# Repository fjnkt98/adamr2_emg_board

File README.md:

# adamr2_emg_board
PCB design project for the Emergency Stop Switch Mechanism of ADAMR2

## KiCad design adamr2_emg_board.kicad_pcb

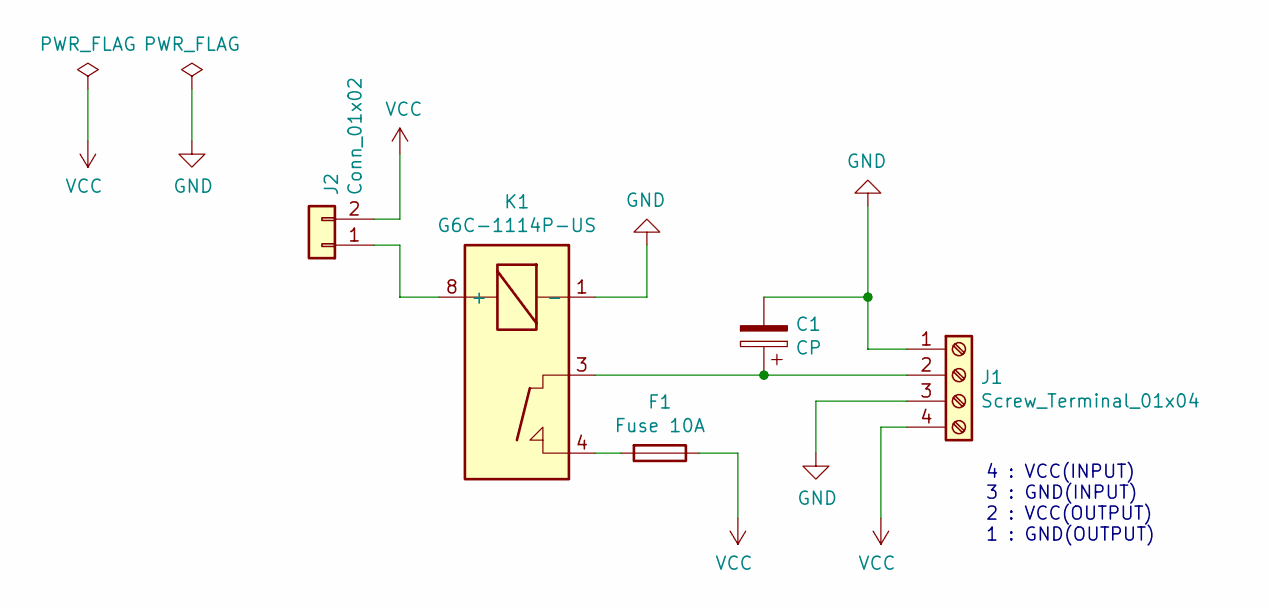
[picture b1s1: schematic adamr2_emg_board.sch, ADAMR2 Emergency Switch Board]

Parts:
C1: CP; UFG1H102MHM
F1: Fuse 10A; F-60-A
J1: Screw_Terminal_01x04; OSTYK21104030
J2: Conn_01x02; JST_XH_B2B-XH-A_1x02_P2.50mm_Vertical
K1: G6C-1114P-US

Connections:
GND: C1.2, J1.1, J1.3, K1.1 (-)
unnamed: C1.1, J1.2, K1.3
unnamed: F1.2, K1.4
unnamed: J2.1, K1.8 (+)
VCC: F1.1, J1.4, J2.2

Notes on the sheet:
4 : VCC(INPUT) 3 : GND(INPUT) 2 : VCC(OUTPUT) 1 : GND(OUTPUT)

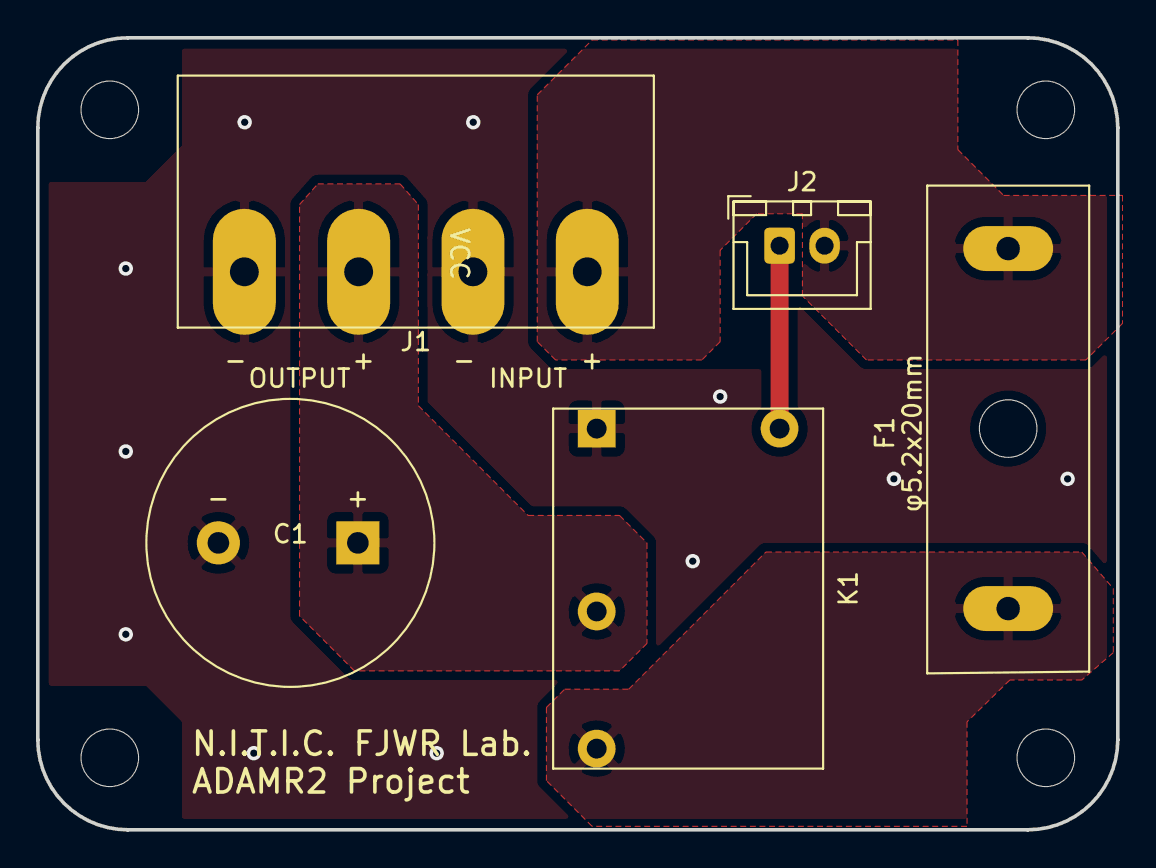
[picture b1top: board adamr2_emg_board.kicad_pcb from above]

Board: 2 copper layers, 60.0 x 44.0 mm, 5 parts (0 on the bottom side), 5 nets.

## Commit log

2020-08-03 Add: Initialize
2020-08-03 Update: フットプリントに3Dモデルを紐つけた
2020-08-03 Add: 4極ターミナルのフットプリント
2020-08-03 Add: 4極ターミナルの3Dモデルを追加
2020-08-03 Update: 3Dモデルを紐つけた
2020-08-03 Add: ミスミで買えるヒューズホルダ
2020-08-03 Add: ヒューズホルダの3Dモデル
2020-08-03 Update: ヒューズホルダの種類を変更した
2020-08-05 Update: フットプリントのパッドの形状を楕円に変更
2020-08-05 Update: 表面をVCC，裏面をGNDのベタにした
2020-08-07 Update: DRCに引っかかったので修正
    禁止領域の設定が配線と被っていたので形状を調整した
2020-08-10 Update: シルクを少し調整，寸法線を追加
2020-08-31 Add: ガーバーファイル
2020-09-04 Add: コンデンサのフットプリント
2020-09-04 Update: コンデンサを入れた
2020-09-04 Update: 3Dモデルを追加
2020-09-04 Update: コンデンサの3Dモデルを反映
2020-09-04 Update: ネジ穴の周りのベタグランドを裏面も除去
2020-09-04 Add: ガーバーデータ
